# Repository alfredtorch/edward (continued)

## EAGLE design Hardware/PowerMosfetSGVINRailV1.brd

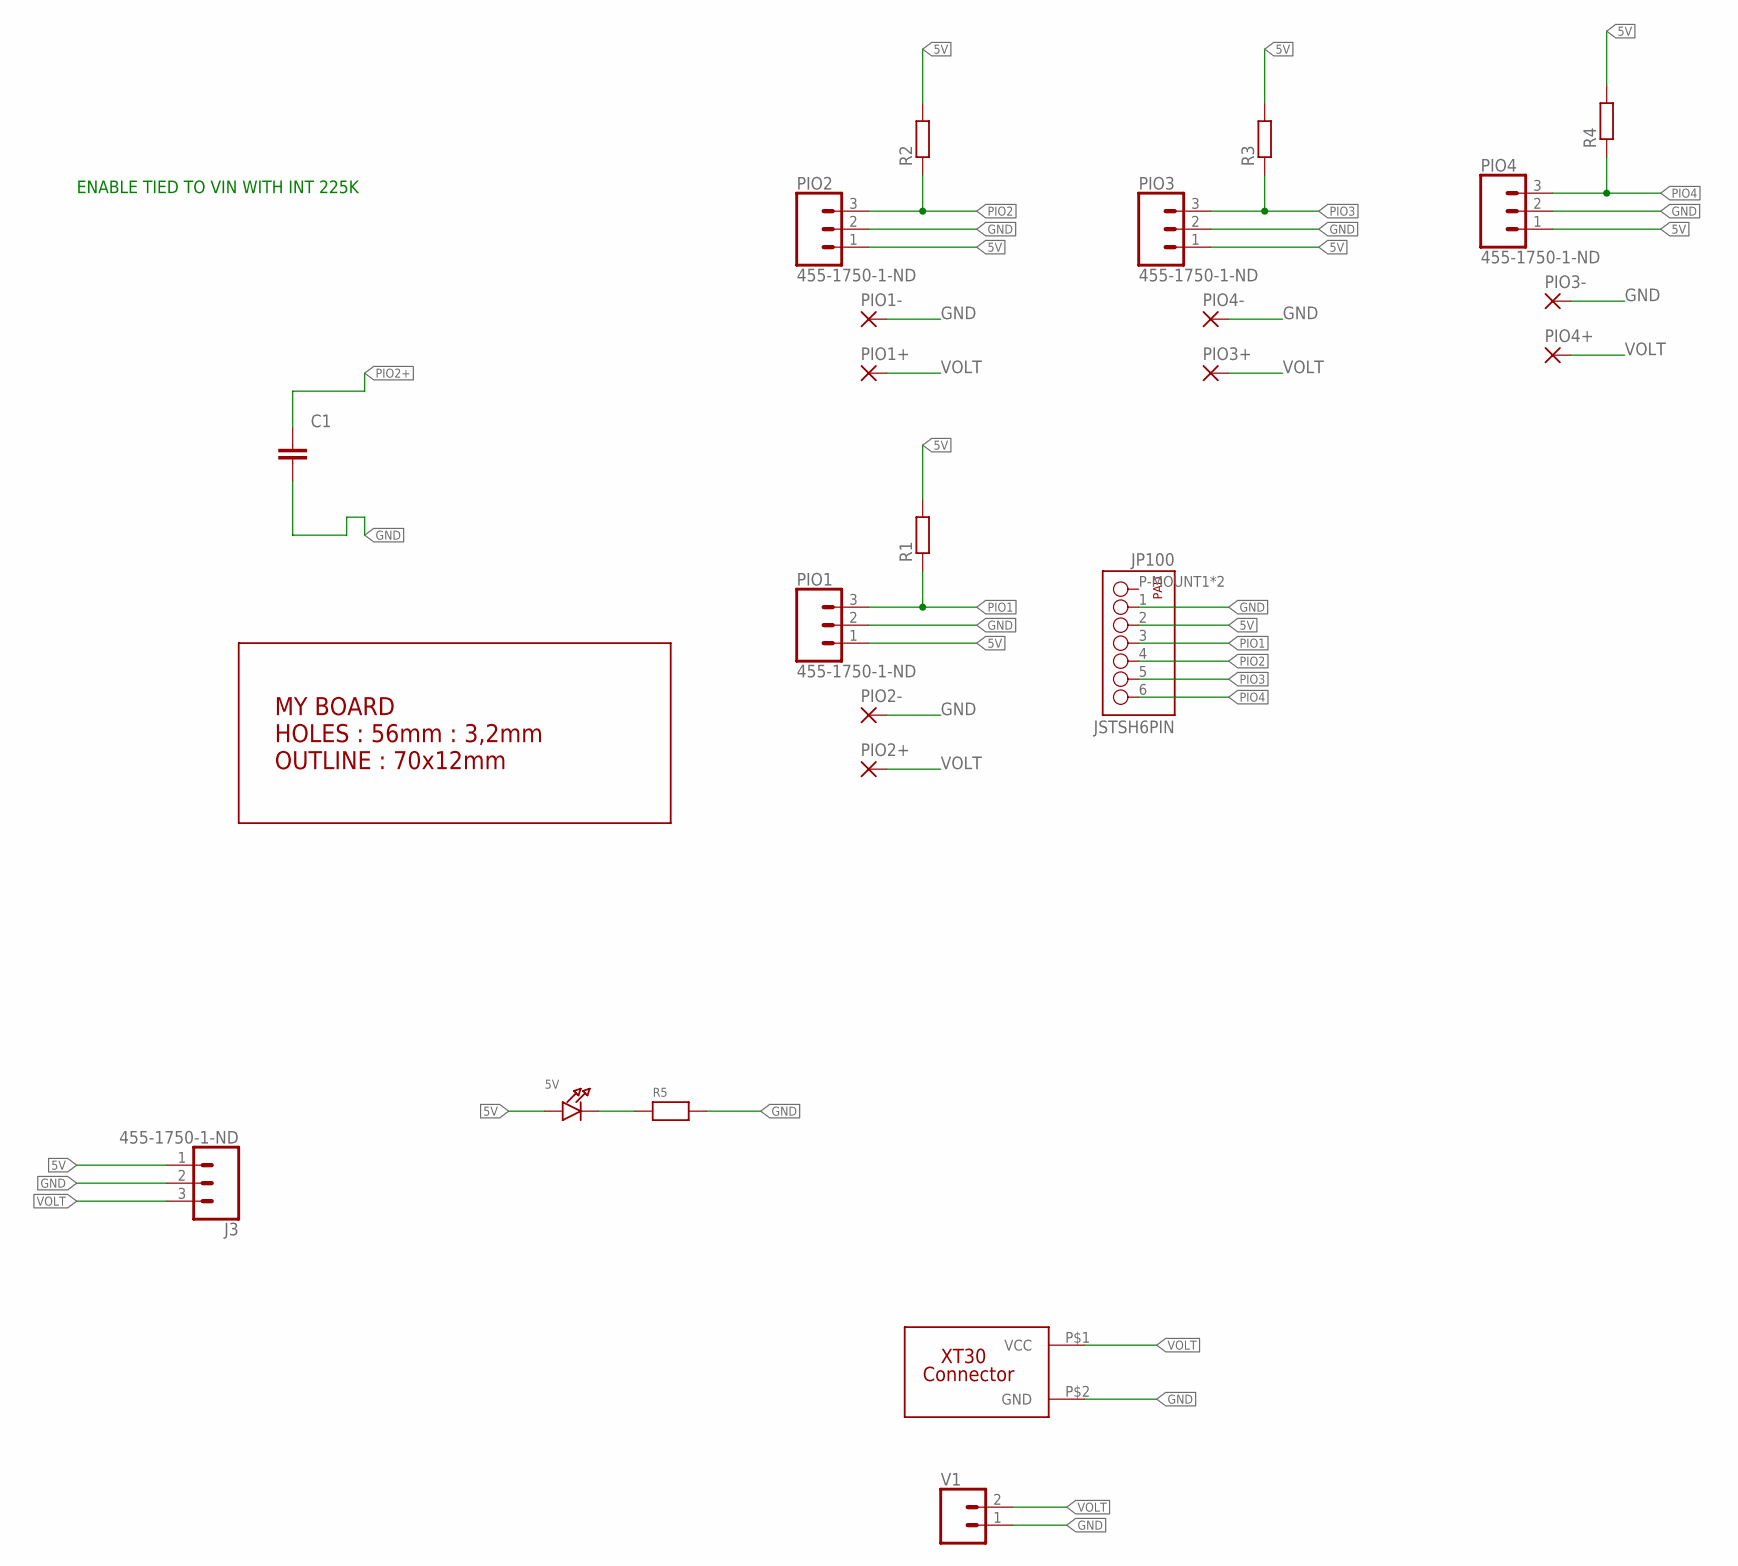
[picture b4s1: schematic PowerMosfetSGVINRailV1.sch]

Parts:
5V: LED0805; CHIPLED_0805
C1: CAPACITOR_NPOL-0805; C805
J3: 455-1750-1-ND; 1X03
JP100: JSTSH6PIN; SM06B-SRSS-TB
PIO1, PIO2, PIO3, PIO4: 455-1750-1-ND; 1X03
PIO1+, PIO1-, PIO2+, PIO2-, PIO3+, PIO3-, PIO4+, PIO4-: 3,17/1,3
R1, R2, R3, R4: RESISTORR805-0805; R805
R5: RESISTOR0805; 0805
U$2: BOARD70X12HOES; BOARD70X12
U$6: XT30; XT30-VERT
V1: CONN_023.5MM; SCREWTERMINAL-3.5MM-2

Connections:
5V: 5V.A, J3.1, JP100.2, PIO1.1, PIO2.1, PIO3.1, PIO4.1, R1.2, R2.2, R3.2, R4.2
GND: C1.2, J3.2, JP100.1, PIO1.2, PIO1-.1, PIO2.2, PIO2-.1, PIO3.2, PIO3-.1, PIO4.2, PIO4-.1, R5.2, U$6.P$2 (GND), V1.1
unnamed: 5V.C, R5.1
PIO1: JP100.3, PIO1.3, R1.1
PIO2: JP100.4, PIO2.3, R2.1
PIO2+: C1.1
PIO3: JP100.5, PIO3.3, R3.1
PIO4: JP100.6, PIO4.3, R4.1
VOLT: J3.3, PIO1+.1, PIO2+.1, PIO3+.1, PIO4+.1, U$6.P$1 (VCC), V1.2

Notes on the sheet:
ENABLE TIED TO VIN WITH INT 225K

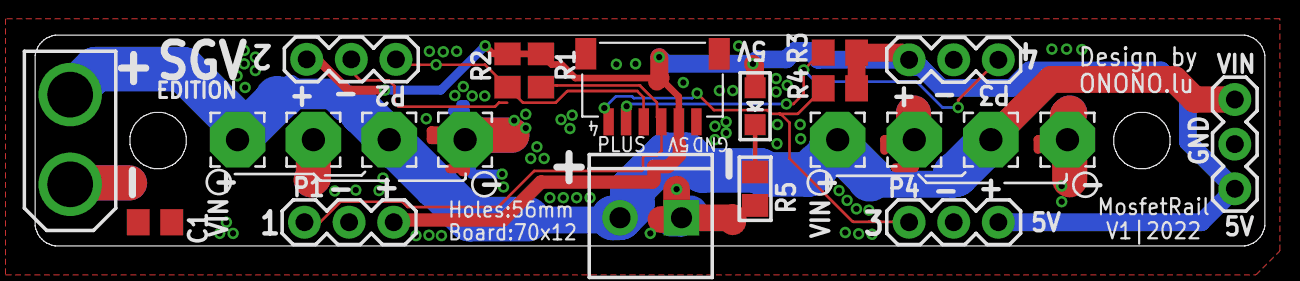
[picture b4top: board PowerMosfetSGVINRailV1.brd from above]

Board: 2 copper layers, 70.0 x 12.0 mm, 24 parts (0 on the bottom side), 8 nets.
